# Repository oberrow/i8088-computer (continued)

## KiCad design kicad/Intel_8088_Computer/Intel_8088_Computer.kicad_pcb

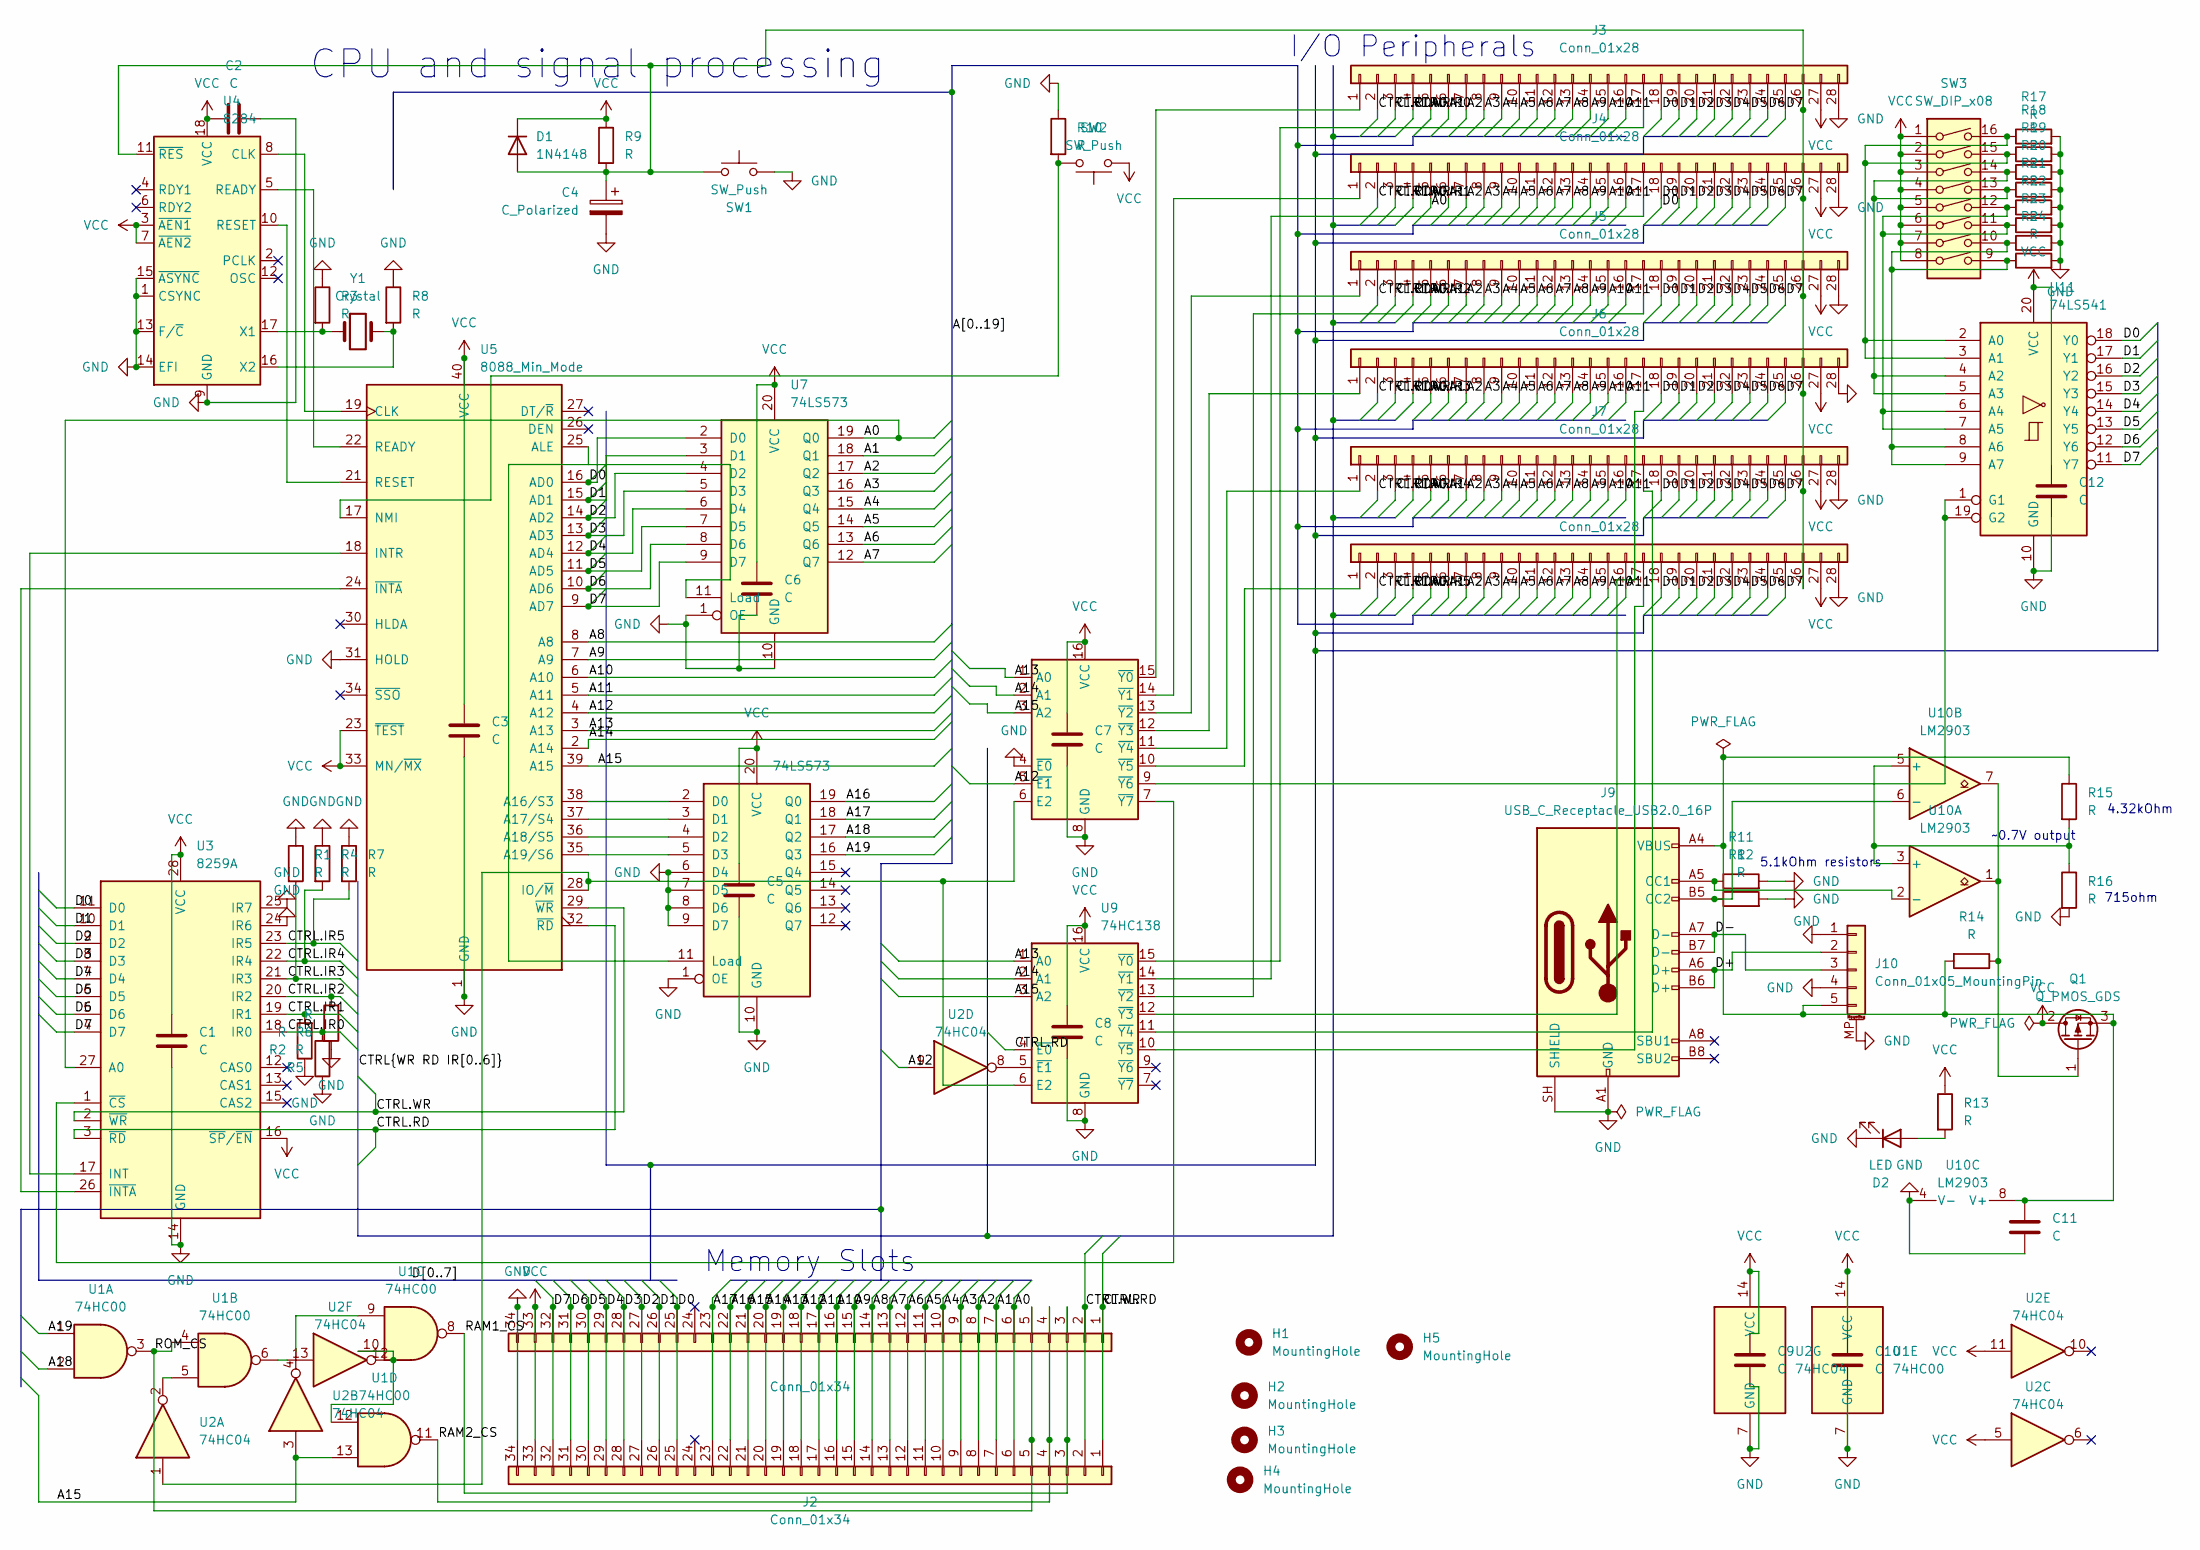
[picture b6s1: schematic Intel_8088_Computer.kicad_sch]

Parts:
C1, C2, C3, C5, C6, C7, C8, C9, C10, C11, C12: C; C_Disc_D5.0mm_W2.5mm_P2.50mm
C4: C_Polarized; CP_Radial_D5.0mm_P2.00mm
D1: 1N4148; D_DO-35_SOD27_P7.62mm_Horizontal
D2: LED; LED_D3.0mm
H1, H2, H3, H4, H5: MountingHole; MountingHole_2.2mm_M2
J1, J2: Conn_01x34; PinHeader_2x17_P2.54mm_Vertical
J3, J4, J5, J6, J7, J8: Conn_01x28; PinHeader_2x14_P2.54mm_Vertical
J9: USB_C_Receptacle_USB2.0_16P; USB_C_Receptacle_GCT_USB4085
J10: Conn_01x05_MountingPin; Molex_200528-0050_1x05-1MP_P1.00mm_Horizontal
Q1: Q_PMOS_GDS; TO-220-3_Vertical
R1, R2, R3, R4, R5, R6, R7, R8, R9, R10, R11, R12, R13, R14, R15, R16, R17, R18, R19, R20, R21, R22, R23, R24: R; R_Axial_DIN0207_L6.3mm_D2.5mm_P7.62mm_Horizontal
SW1, SW2: SW_Push; SW_PUSH_6mm
SW3: SW_DIP_x08; SW_DIP_SPSTx08_Slide_6.7x21.88mm_W7.62mm_P2.54mm_LowProfile
U1: 74HC00; DIP-14_W7.62mm
U2: 74HC04; DIP-14_W7.62mm
U3: 8259A; DIP-28_W15.24mm
U4: 8284; DIP-18_W7.62mm
U5: 8088_Min_Mode; DIP-40_W15.24mm
U6, U7: 74LS573; DIP-20_W7.62mm
U8, U9: 74HC138; DIP-16_W7.62mm
U10: LM2903; DIP-8_W7.62mm
U11: 74LS541; DIP-20_W7.62mm
Y1: Crystal; Crystal_HC49-U_Vertical

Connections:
/A0: J1.6, J2.6, J3.5, J4.5, J5.5, J6.5, J7.5, J8.5, U3.27 (A0), U7.19 (Q0)
/A1: J1.7, J2.7, J3.6, J4.6, J5.6, J6.6, J7.6, J8.6, U7.18 (Q1)
/A2: J1.8, J2.8, J3.7, J4.7, J5.7, J6.7, J7.7, J8.7, U7.17 (Q2)
/A3: J1.9, J2.9, J3.8, J4.8, J5.8, J6.8, J7.8, J8.8, U7.16 (Q3)
/A4: J1.10, J2.10, J3.9, J4.9, J5.9, J6.9, J7.9, J8.9, U7.15 (Q4)
/A5: J1.11, J2.11, J3.10, J4.10, J5.10, J6.10, J7.10, J8.10, U7.14 (Q5)
/A6: J1.12, J2.12, J3.11, J4.11, J5.11, J6.11, J7.11, J8.11, U7.13 (Q6)
/A7: J1.13, J2.13, J3.12, J4.12, J5.12, J6.12, J7.12, J8.12, U7.12 (Q7)
/A8: J1.14, J2.14, J3.13, J4.13, J5.13, J6.13, J7.13, J8.13, U5.8 (A8)
/A9: J1.15, J2.15, J3.14, J4.14, J5.14, J6.14, J7.14, J8.14, U5.7 (A9)
/A10: J1.16, J2.16, J3.15, J4.15, J5.15, J6.15, J7.15, J8.15, U5.6 (A10)
/A11: J1.17, J2.17, J3.16, J4.16, J5.16, J6.16, J7.16, J8.16, U5.5 (A11)
/A12: J1.18, J2.18, U2.9, U5.4 (A12), U8.5 (~E1)
/A13: J1.19, J2.19, U5.3 (A13), U8.1 (A0), U9.1 (A0)
/A14: J1.20, J2.20, U5.2 (A14), U8.2 (A1), U9.2 (A1)
/A15: J1.21, J2.21, U1.13, U2.3, U5.39 (A15), U8.3 (A2), U9.3 (A2)
/A16: J1.22, J2.22, U6.19 (Q0)
/A17: J1.23, J2.23, U6.18 (Q1)
/A18: U1.2, U6.17 (Q2)
/A19: U1.1, U6.16 (Q3)
/CTRL.IR0: J3.4, R5.2, U3.18 (IR0)
/CTRL.IR1: J4.4, R2.2, U3.19 (IR1)
/CTRL.IR2: J5.4, R6.2, U3.20 (IR2)
/CTRL.IR3: J6.4, R1.2, U3.21 (IR3)
/CTRL.IR4: J7.4, R4.2, U3.22 (IR4)
/CTRL.IR5: J8.4, R7.2, U3.23 (IR5)
/CTRL.RD: J1.1, J2.1, J3.2, J4.2, J5.2, J6.2, J7.2, J8.2, U3.3 (~RD), U5.32 (~RD), U9.4 (~E0)
/CTRL.WR: J1.2, J2.2, J3.3, J4.3, J5.3, J6.3, J7.3, J8.3, U3.2 (~WR), U5.29 (~WR)
/D0: J1.25, J2.25, J3.18, J4.18, J5.18, J6.18, J7.18, J8.18, U3.11 (D0), U5.16 (AD0), U7.2 (D0), U11.18 (Y0)
/D1: J1.26, J2.26, J3.19, J4.19, J5.19, J6.19, J7.19, J8.19, U3.10 (D1), U5.15 (AD1), U7.3 (D1), U11.17 (Y1)
/D2: J1.27, J2.27, J3.20, J4.20, J5.20, J6.20, J7.20, J8.20, U3.9 (D2), U5.14 (AD2), U7.4 (D2), U11.16 (Y2)
/D3: J1.28, J2.28, J3.21, J4.21, J5.21, J6.21, J7.21, J8.21, U3.8 (D3), U5.13 (AD3), U7.5 (D3), U11.15 (Y3)
/D4: J1.29, J2.29, J3.22, J4.22, J5.22, J6.22, J7.22, J8.22, U3.7 (D4), U5.12 (AD4), U7.6 (D4), U11.14 (Y4)
/D5: J1.30, J2.30, J3.23, J4.23, J5.23, J6.23, J7.23, J8.23, U3.6 (D5), U5.11 (AD5), U7.7 (D5), U11.13 (Y5)
/D6: J1.31, J2.31, J3.24, J4.24, J5.24, J6.24, J7.24, J8.24, U3.5 (D6), U5.10 (AD6), U7.8 (D6), U11.12 (Y6)
/D7: J1.32, J2.32, J3.25, J4.25, J5.25, J6.25, J7.25, J8.25, U3.4 (D7), U5.9 (AD7), U7.9 (D7), U11.11 (Y7)
/D+: J9.A6 (D+), J9.B6 (D+), J10.2
/D-: J9.A7 (D-), J9.B7 (D-), J10.3
/RAM1_CS: J1.3, J2.3, U1.8
/RAM2_CS: J1.4, J2.4, U1.11
/ROM_CS: J1.5, J2.5, U1.3, U1.4
GND: C1.2, C2.2, C3.2, C4.2, C5.2, C6.2, C7.2, C8.2, C9.2, C10.2, C11.2, C12.2, D2.1 (K), J1.34, J2.34, J3.28, J4.28, J5.28, J6.28, J7.28, J8.28, J9.A1 (GND), J9.A12 (GND), J9.B1 (GND), J9.B12 (GND), J9.SH (SHIELD), J10.1, J10.4, J10.MP (MountPin), R1.1, R2.1, R3.1, R4.1, R5.1, R6.1, R7.1, R8.1, R10.1, R11.2, R12.2, R16.2, R17.2, R18.2, R19.2, R20.2, R21.2, R22.2, R23.2, R24.2, SW1.2, U1.7 (GND), U2.7 (GND), U3.14 (GND), U3.24 (IR6), U3.25 (IR7), U4.1 (CSYNC), U4.9 (GND), U4.13 (F/~C), U4.14 (EFI), U4.15 (~ASYNC), U5.1 (GND), U5.20 (GND), U5.31 (HOLD), U6.1 (OE), U6.6 (D4), U6.7 (D5), U6.8 (D6), U6.9 (D7), U6.10 (GND), U7.1 (OE), U7.10 (GND), U8.4 (~E0), U8.8 (GND), U9.8 (GND), U10.4 (V-), U11.10 (GND)
unnamed: C4.1, D1.2 (A), J3.26, J4.26, J5.26, J6.26, J7.26, J8.26, R9.2, SW1.1, U4.11 (~RES)
unnamed: D2.2 (A), R13.2
unnamed: J3.1, U8.15 (~Y0)
unnamed: J3.17, U9.15 (~Y0)
unnamed: J4.1, U8.14 (~Y1)
unnamed: J4.17, U9.14 (~Y1)
unnamed: J5.1, U8.13 (~Y2)
unnamed: J5.17, U9.13 (~Y2)
unnamed: J6.1, U8.12 (~Y3)
unnamed: J6.17, U9.12 (~Y3)
unnamed: J7.1, U8.11 (~Y4)
unnamed: J7.17, U9.11 (~Y4)
unnamed: J8.1, U8.10 (~Y5)
unnamed: J8.17, U9.10 (~Y5)
unnamed: J9.A5 (CC1), R11.1, U10.2 (-)
unnamed: J9.B5 (CC2), R12.1, U10.6 (-)
unnamed: C11.1, J9.A4 (VBUS), J9.A9 (VBUS), J9.B4 (VBUS), J9.B9 (VBUS), J10.5, Q1.3 (S), R14.2, R15.1, U10.8 (V+)
unnamed: Q1.1 (G), R14.1, U10.1, U10.7
unnamed: U1.5, U2.2
unnamed: U1.6, U2.13
unnamed: U1.9, U2.4
unnamed: U1.10, U1.12, U2.12
unnamed: U3.17 (INT), U5.18 (INTR)
unnamed: U3.1 (~CS), U8.7 (~Y7)
unnamed: U3.26 (~INTA), U5.24 (~INTA)
unnamed: U4.8 (CLK), U5.19 (CLK)
unnamed: U4.5 (READY), U5.22 (READY)
unnamed: U4.10 (RESET), U5.21 (RESET)
unnamed: R3.2, U4.17 (X1), Y1.1
unnamed: R8.2, U4.16 (X2), Y1.2
unnamed: U5.38 (A16/S3), U6.2 (D0)
unnamed: U5.37 (A17/S4), U6.3 (D1)
unnamed: U5.36 (A18/S5), U6.4 (D2)
unnamed: U5.35 (A19/S6), U6.5 (D3)
unnamed: U5.25 (ALE), U6.11 (Load), U7.11 (Load)
unnamed: U2.1, U5.28 (IO/~M), U8.6 (E2), U9.6 (E2)
unnamed: R10.2, SW2.2, U5.17 (NMI)
unnamed: U2.8, U9.5 (~E1)
unnamed: R15.2, R16.1, U10.3 (+), U10.5 (+)
unnamed: R17.1, R18.1, SW3.15, SW3.16, U11.2 (A0), U11.3 (A1)
unnamed: R19.1, R20.1, SW3.13, SW3.14, U11.4 (A2), U11.5 (A3)
unnamed: R21.1, R22.1, SW3.11, SW3.12, U11.6 (A4), U11.7 (A5)
unnamed: R23.1, R24.1, SW3.9, SW3.10, U11.8 (A6), U11.9 (A7)
unnamed: U8.9 (~Y6), U11.1 (G1), U11.19 (G2)
VCC: C1.1, C2.1, C3.1, C5.1, C6.1, C7.1, C8.1, C9.1, C10.1, C12.1, D1.1 (K), J1.33, J2.33, J3.27, J4.27, J5.27, J6.27, J7.27, J8.27, Q1.2 (D), R9.1, R13.1, SW2.1, SW3.1, SW3.2, SW3.3, SW3.4, SW3.5, SW3.6, SW3.7, SW3.8, U1.14 (VCC), U2.5, U2.11, U2.14 (VCC), U3.16 (~SP/~EN), U3.28 (VCC), U4.3 (~AEN1), U4.7 (~AEN2), U4.18 (VCC), U5.23 (~TEST), U5.33 (MN/~MX), U5.40 (VCC), U6.20 (VCC), U7.20 (VCC), U8.16 (VCC), U9.16 (VCC), U11.20 (VCC)

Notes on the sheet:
Memory Slots
CPU and signal processing
I/O Peripherals
4.32kOhm
715ohm
5.1kOhm resistors
~0.7V output

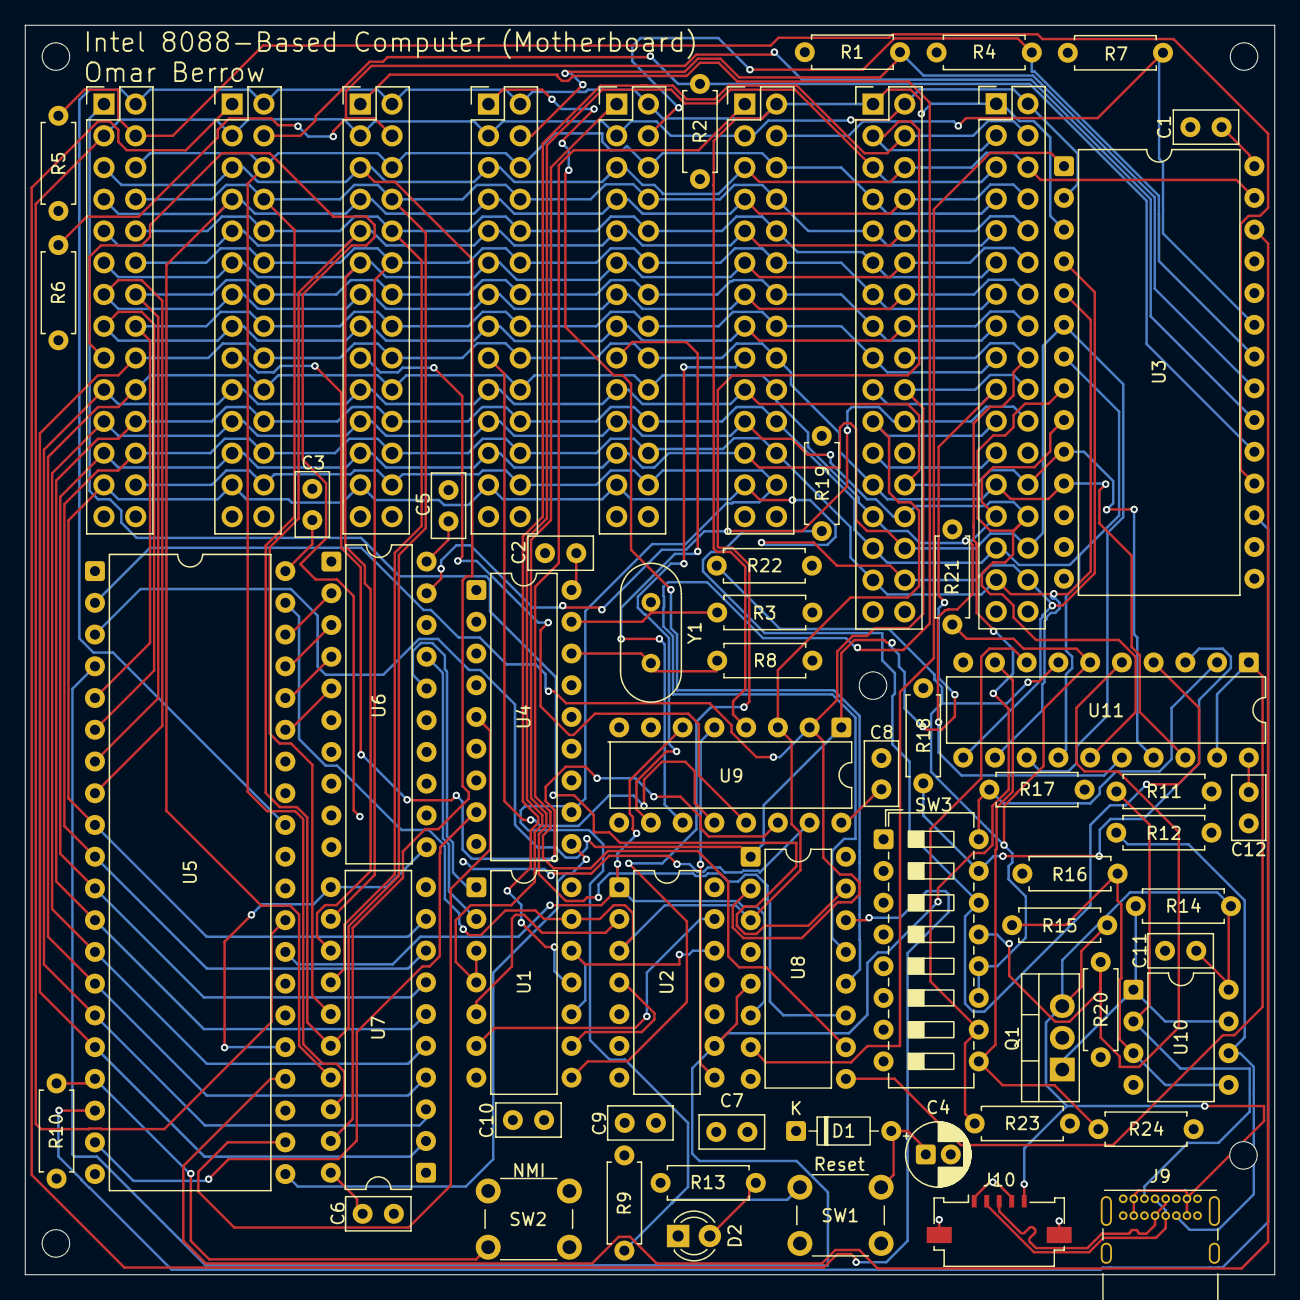
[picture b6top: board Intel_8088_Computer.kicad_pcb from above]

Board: 4 copper layers, 100.0 x 100.0 mm, 69 parts (0 on the bottom side), 87 nets.

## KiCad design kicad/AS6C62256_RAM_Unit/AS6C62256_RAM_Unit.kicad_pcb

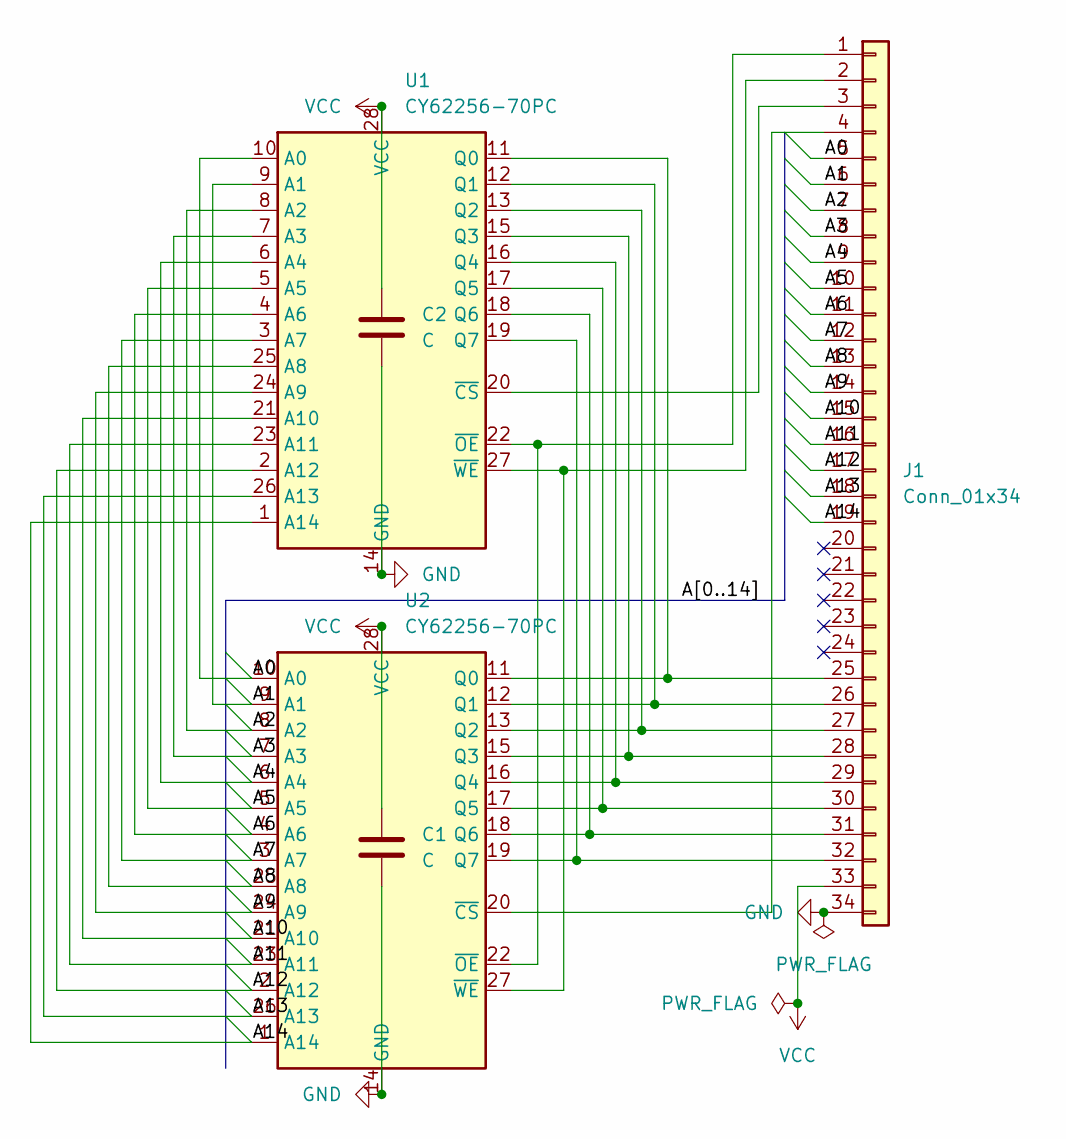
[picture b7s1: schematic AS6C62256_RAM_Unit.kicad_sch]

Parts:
C1, C2: C; C_Disc_D5.0mm_W2.5mm_P2.50mm
J1: Conn_01x34; PinHeader_2x17_P2.54mm_Vertical
U1, U2: CY62256-70PC; DIP-28_W15.24mm

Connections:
/A0: J1.5, U1.10 (A0), U2.10 (A0)
/A1: J1.6, U1.9 (A1), U2.9 (A1)
/A2: J1.7, U1.8 (A2), U2.8 (A2)
/A3: J1.8, U1.7 (A3), U2.7 (A3)
/A4: J1.9, U1.6 (A4), U2.6 (A4)
/A5: J1.10, U1.5 (A5), U2.5 (A5)
/A6: J1.11, U1.4 (A6), U2.4 (A6)
/A7: J1.12, U1.3 (A7), U2.3 (A7)
/A8: J1.13, U1.25 (A8), U2.25 (A8)
/A9: J1.14, U1.24 (A9), U2.24 (A9)
/A10: J1.15, U1.21 (A10), U2.21 (A10)
/A11: J1.16, U1.23 (A11), U2.23 (A11)
/A12: J1.17, U1.2 (A12), U2.2 (A12)
/A13: J1.18, U1.26 (A13), U2.26 (A13)
/A14: J1.19, U1.1 (A14), U2.1 (A14)
GND: C1.2, C2.2, J1.34, U1.14 (GND), U2.14 (GND)
unnamed: J1.1, U1.22 (~OE), U2.22 (~OE)
unnamed: J1.2, U1.27 (~WE), U2.27 (~WE)
unnamed: J1.3, U1.20 (~CS)
unnamed: J1.4, U2.20 (~CS)
unnamed: J1.25, U1.11 (Q0), U2.11 (Q0)
unnamed: J1.26, U1.12 (Q1), U2.12 (Q1)
unnamed: J1.27, U1.13 (Q2), U2.13 (Q2)
unnamed: J1.28, U1.15 (Q3), U2.15 (Q3)
unnamed: J1.29, U1.16 (Q4), U2.16 (Q4)
unnamed: J1.30, U1.17 (Q5), U2.17 (Q5)
unnamed: J1.31, U1.18 (Q6), U2.18 (Q6)
unnamed: J1.32, U1.19 (Q7), U2.19 (Q7)
VCC: C1.1, C2.1, J1.33, U1.28 (VCC), U2.28 (VCC)

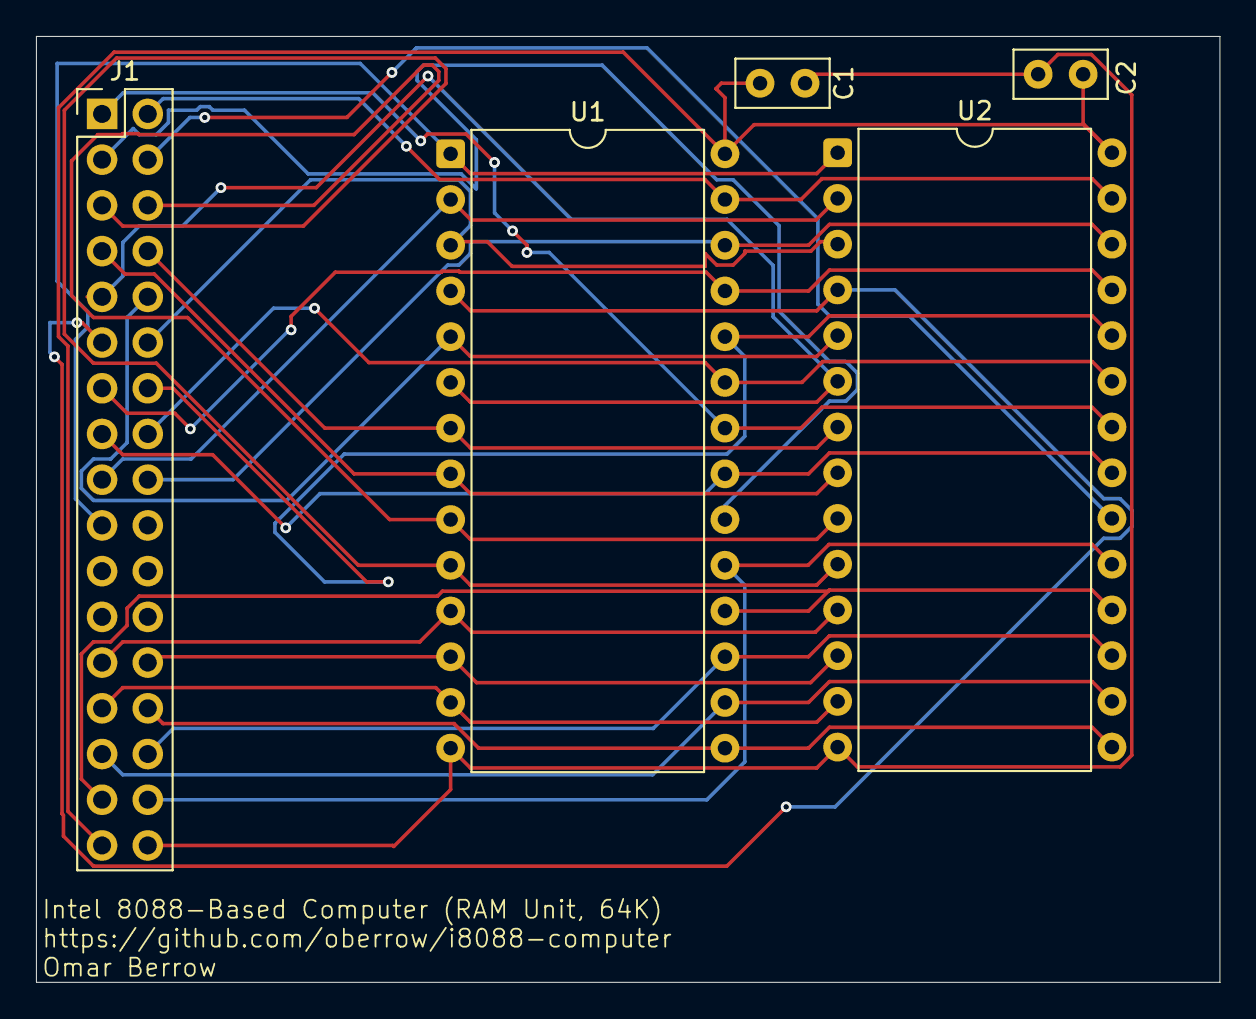
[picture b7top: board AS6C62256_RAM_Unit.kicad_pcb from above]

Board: 2 copper layers, 65.8 x 52.5 mm, 5 parts (0 on the bottom side), 29 nets.

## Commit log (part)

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2026-04-25 misc: include .data in linker script properly
2026-04-25 io: add I/O base macros to io.h
2026-04-25 misc: add set_es and set_ds functions
2026-04-25 misc: use __far attribute in many places
2026-04-25 pic: add pic code
2026-04-25 misc: add CPU 8086 directive to all assembly code
2026-04-25 irq: setup IVT
2026-04-26 misc: add flags manipulation helpers and hlt helper
2026-04-26 irq: add pic_clear_mask
2026-04-26 uart: add basic uart driver
2026-04-26 misc: initialize uart in main.c
2026-04-26 irq: implement spurious irq handler
2026-04-26 misc: add delay_cycles function
    This function assumes an 8mHZ clock. This might not always be true, if i decide to underclock my 8088-2.
2026-04-26 lcd: implement 1602 LCD driver
    Drives the HD44780U chip, specifically.
2026-04-26 misc: add phony targets to Makefile
2026-04-28 misc: fix bug in linker script
2026-04-28 misc: halt on fatal exception
2026-04-28 misc: add .flash section to linker script
2026-04-28 irq: fix bug with int_handler_common
2026-04-28 misc: fill ROM binary with 0xff instead of 0x00
2026-04-28 misc: fix bug with reset vector code
2026-04-28 misc: print hello world on entry
2026-04-29 misc: fix relocation errors
2026-04-29 timer: add clock source
2026-04-29 lcd: use delay_ms
2026-04-29 misc: do not print CRNL on LCD screen
2026-04-29 misc: write error messages to uart on exception
2026-04-29 misc: move code segment to 0xc000 to account for ROM changing place in the memory map
2026-05-18 misc: add gdbstub and fix bugs
2026-05-18 uart: change divisor to account for changed 16550 crystal frequency
    Physically, the crystal was going to be a 12mhz crystal, but it is being changed to a standard 1.8432mhz crystal.
2026-06-29 io: adapt to new motherboard chipset and address decoding logic and implement an i8255 driver
    The PCB version of the breadboard computer differs from the breadboard greatly. Firstly, the address decoding logic was essentially overhauled, and probing was supported. I/O Slots exist on the PCB v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
2026-06-29 spi: add bitbanging code for SPI
2026-06-29 spi: add spi_pulse
2026-06-29 sd: add SPI SD card driver
    Code is currently untested
2026-06-30 misc: fix bug with memcpy_far
2026-06-30 uart: fix bug in driver
2026-06-30 io: fix bug in probing code
2026-06-30 misc: fix bug in entry code
2026-06-30 misc: add bootloader handoff code
    Sector zero of the SD card is the boot sector. Trailing bytes should be 0x8088 (LE) to be recognized as a bootable device in the eyes of this firmware. This commit also generates a memory map and I/O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
2026-06-30 misc: make flat assembly test occupy the full 256KiB of flash
